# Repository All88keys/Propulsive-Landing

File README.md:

# propulsive-landing
 Arduino Script for HERMES rocket tests

## v0
Test scripts for LEMNOS3 board for Hermes I ("Agon0")

## v1
Test scripts for LEMNOS3 board for Hermes I ("Agon1")

## LEMNOS3
Autodesk EAGLE project for LEMNOS3, logic board design for Hermes I. 
- [Link to EAGLE download](https://www.autodesk.com/products/eagle/overview?plc=F360&term=1-YEAR&support=ADVANCED&quantity=1)
- [Link to MPU 6050](https://www.sparkfun.com/products/11028)

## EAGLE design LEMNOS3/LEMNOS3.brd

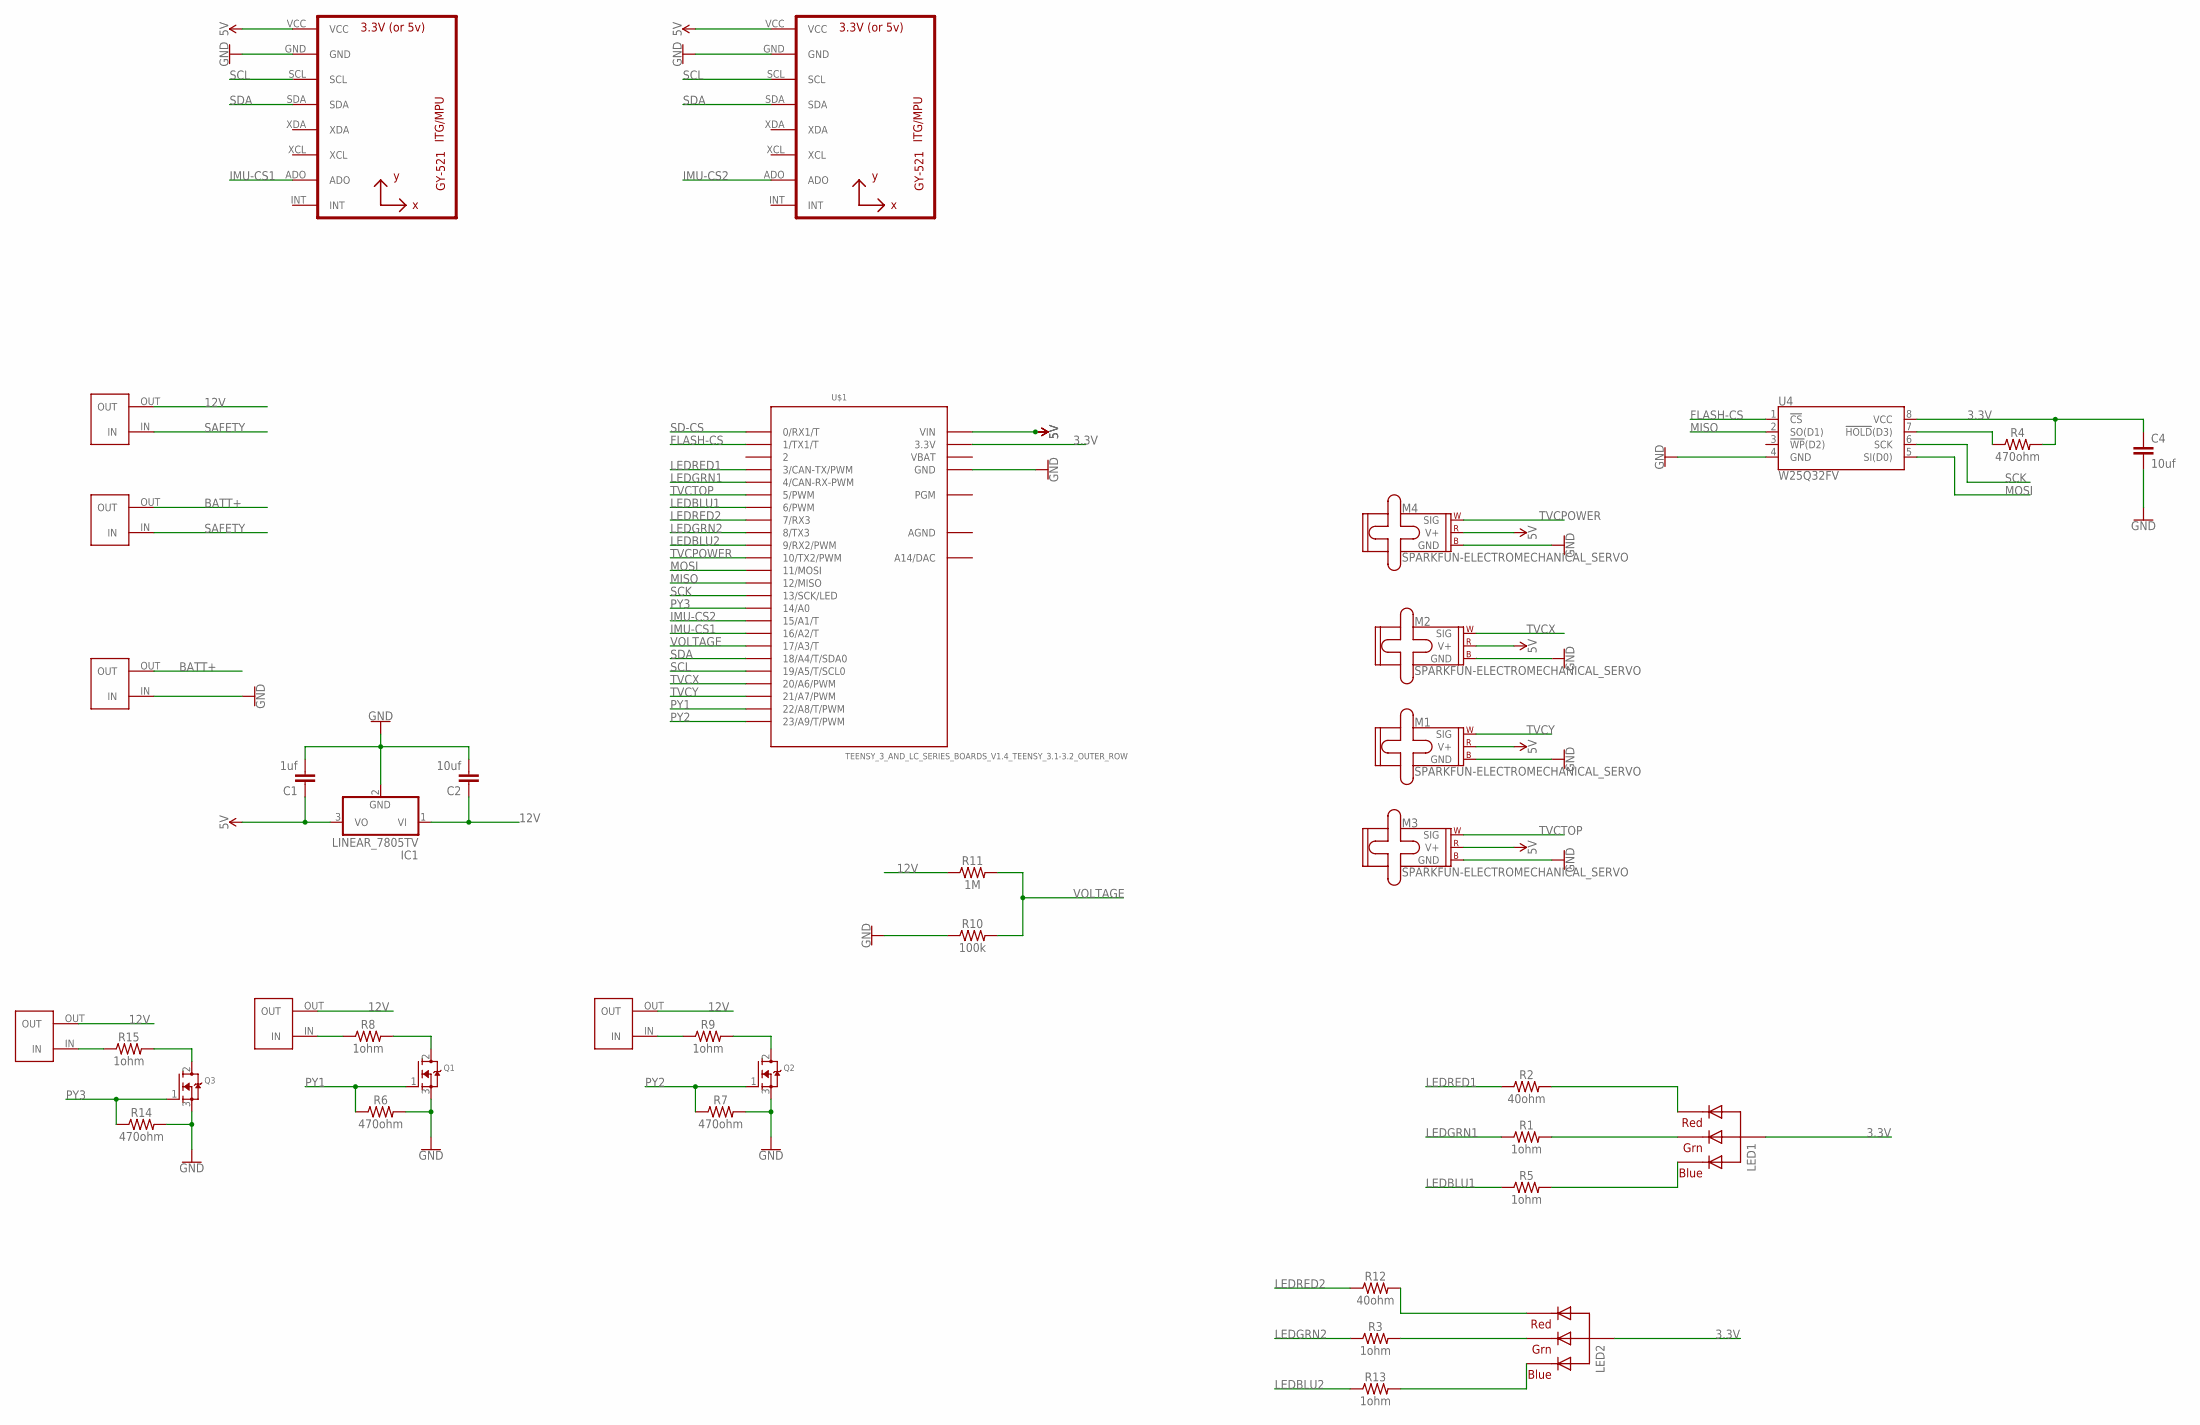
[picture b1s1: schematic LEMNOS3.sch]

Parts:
C1: 1uf; SPARKFUN-CAPACITORS_CAP-PTH-2.54
C2, C4: 10uf; SPARKFUN-CAPACITORS_CAP-PTH-2.54
IC1: LINEAR_7805TV; LINEAR_TO220V
LED1, LED2: RGBLED_CA-5MM; LED5MMRGB
M1, M2, M3, M4: SPARKFUN-ELECTROMECHANICAL_SERVO; SPARKFUN-ELECTROMECHANICAL_1X03
Q1, Q2, Q3: ADAFRUIT_MOSFET-NGDS_TO220V; ADAFRUIT_TO220V
R1, R3, R5, R8, R9, R13, R15: 1ohm; SPARKFUN-RESISTORS_AXIAL-0.3
R2, R12: 40ohm; SPARKFUN-RESISTORS_AXIAL-0.3
R4, R6, R7, R14: 470ohm; SPARKFUN-RESISTORS_AXIAL-0.3
R10: 100k; SPARKFUN-RESISTORS_AXIAL-0.3
R11: 1M; SPARKFUN-RESISTORS_AXIAL-0.3
U1, U2: GY-521_GY-521MPU6050; GY-521_GY-521
U4: W25Q32FV; SPARKFUN-IC-MEMORY_SOIC-8
U$1: TEENSY_3_AND_LC_SERIES_BOARDS_V1.4_TEENSY_3.1-3.2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; TEENSY_3_AND_LC_SERIES_BOARDS_V1.4_TEENSY_3.0-3.2&LC_OUTER_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
U$2, U$3, U$4, U$5, U$6, U$8: BLACKTERMBLOCK_BLACKTERMBLOCK

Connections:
3.3V: C4.1, LED1.2 (VCC), LED2.2 (VCC), R4.P$2 (2), U4.8 (VCC), U$1.3.3V, U$1.3.3V1 (3.3V)
5V: C1.1, IC1.3 (VO), M1.2 (V+), M2.2 (V+), M3.2 (V+), M4.2 (V+), U1.VCC, U2.VCC, U$1.VIN
12V: C2.1, IC1.1 (VI), R11.P$1 (1), U$2.OUT, U$5.OUT, U$6.OUT, U$8.OUT
AGND: U$1.AGND
BATT+: U$3.OUT, U$4.OUT
FLASH-CS: U4.1 (!CS!), U$1.1 (1/TX1/T)
GND: C1.2, C2.2, C4.2, IC1.2 (GND), M1.3 (GND), M2.3 (GND), M3.3 (GND), M4.3 (GND), Q1.3 (S), Q2.3 (S), Q3.3 (S), R6.P$2 (2), R7.P$2 (2), R10.P$1 (1), R14.P$2 (2), U1.GND, U2.GND, U4.4 (GND), U$1.GND, U$1.GND1 (GND), U$3.IN
IMU-CS1: U1.ADO, U$1.16/A2 (16/A2/T)
IMU-CS2: U2.ADO, U$1.15/A1 (15/A1/T)
LEDBLU1: R5.P$1 (1), U$1.6 (6/PWM)
LEDBLU2: R13.P$1 (1), U$1.9 (9/RX2/PWM)
LEDGRN1: R1.P$1 (1), U$1.4 (4/CAN-RX-PWM)
LEDGRN2: R3.P$1 (1), U$1.8 (8/TX3)
LEDRED1: R2.P$1 (1), U$1.3 (3/CAN-TX/PWM)
LEDRED2: R12.P$1 (1), U$1.7 (7/RX3)
MISO: U4.2 (SO(D1)), U$1.12 (12/MISO)
MOSI: U4.5 (SI(D0)), U$1.11 (11/MOSI)
unnamed: R15.P$1 (1), U$2.IN
unnamed: LED1.1 (RED), R2.P$2 (2)
unnamed: R4.P$1 (1), U4.7 (!HOLD!(D3))
unnamed: LED1.3 (GREEN), R1.P$2 (2)
unnamed: LED1.4 (BLUE), R5.P$2 (2)
unnamed: R8.P$1 (1), U$5.IN
unnamed: Q1.2 (D), R8.P$2 (2)
unnamed: LED2.1 (RED), R12.P$2 (2)
unnamed: R9.P$1 (1), U$6.IN
unnamed: Q2.2 (D), R9.P$2 (2)
unnamed: LED2.3 (GREEN), R3.P$2 (2)
unnamed: LED2.4 (BLUE), R13.P$2 (2)
unnamed: Q3.2 (D), R15.P$2 (2)
PY1: Q1.1 (G), R6.P$1 (1), U$1.22/A8 (22/A8/T/PWM)
PY2: Q2.1 (G), R7.P$1 (1), U$1.23/A9 (23/A9/T/PWM)
PY3: Q3.1 (G), R14.P$1 (1), U$1.14/A0
SAFETY: U$4.IN, U$8.IN
SCK: U4.6 (SCK), U$1.13 (13/SCK/LED)
SCL: U1.SCL, U2.SCL, U$1.19/A5 (19/A5/T/SCL0)
SD-CS: U$1.0 (0/RX1/T)
SDA: U1.SDA, U2.SDA, U$1.18/A4 (18/A4/T/SDA0)
TVCPOWER: M4.1 (SIG), U$1.10 (10/TX2/PWM)
TVCTOP: M3.1 (SIG), U$1.5 (5/PWM)
TVCX: M2.1 (SIG), U$1.20/A6 (20/A6/PWM)
TVCY: M1.1 (SIG), U$1.21/A7 (21/A7/PWM)
VBAT: U$1.VBAT
VOLTAGE: R10.P$2 (2), R11.P$2 (2), U$1.17/A3 (17/A3/T)

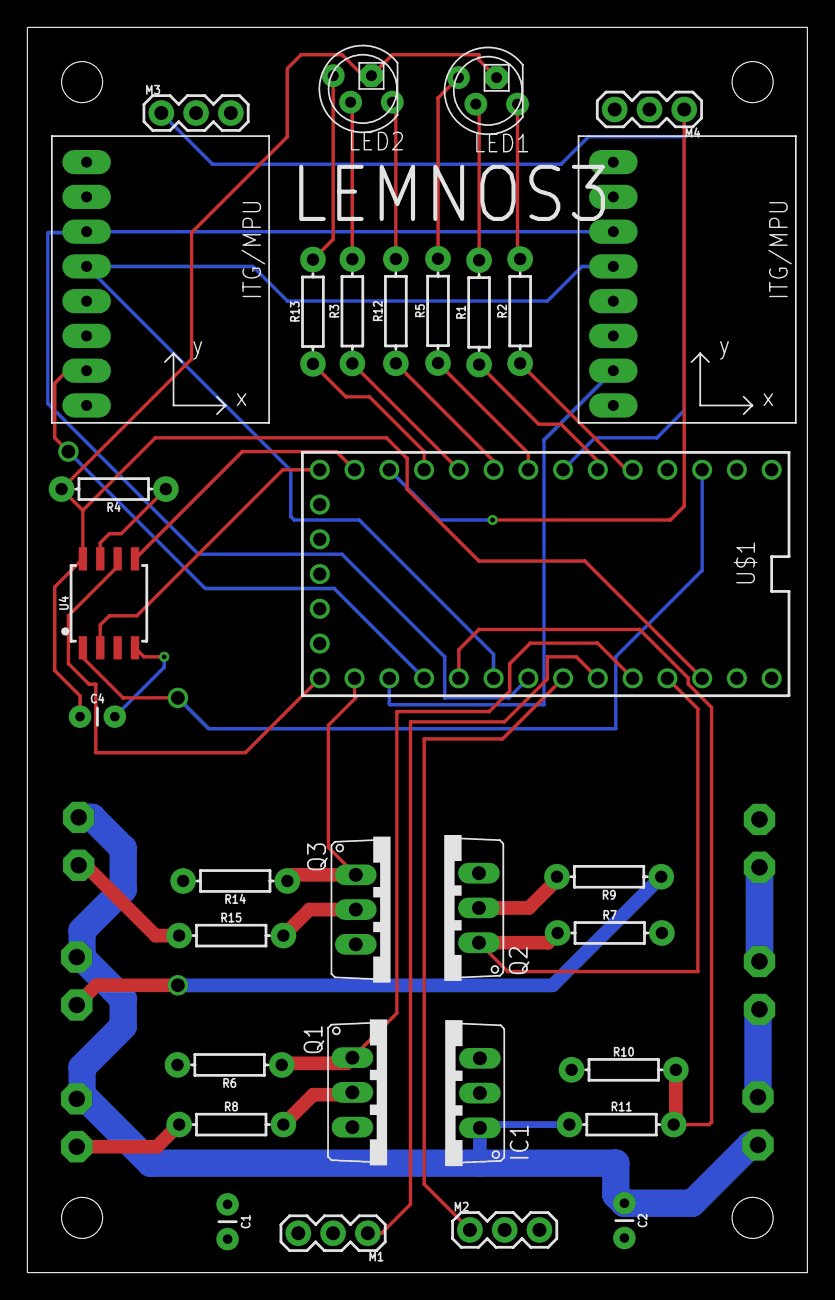
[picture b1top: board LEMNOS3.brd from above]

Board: 2 copper layers, 57.0 x 91.0 mm, 38 parts (0 on the bottom side), 41 nets.

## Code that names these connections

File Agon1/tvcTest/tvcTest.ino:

#include <Servo.h>

//TVC
int TVC_TOP_PIN = 5;
int TVC_X_PIN = 20;
int TVC_Y_PIN = 21;
Servo tvcTop;
Servo tvcX;
Servo tvcY;
int tvcXoffset=85;
int tvcYoffset=83;
//float beta=.9094;
float beta=.6;
int gear=9;
float damper=1.5;
int tvcDelay=10;

long uLast [2]={0, 0};



void setup() {
  // put your setup code here, to run once:
  tvcX.attach(TVC_X_PIN);
  tvcY.attach(TVC_Y_PIN);
  tvcTop.attach(TVC_TOP_PIN);
}

void loop() {
  // put your main code here, to run repeatedly:
    tvc(0, 0, beta, tvcDelay*100);
    /*
    tvc(30, 0, beta, tvcDelay*100);
    tvc(-30, 0, beta, tvcDelay*100);
    tvc(0, 0, beta, tvcDelay*100);
    tvc(0, 30, beta, tvcDelay*100);
    tvc(0, -30, beta, tvcDelay*100);
    tvc(0, 0, beta, tvcDelay*100);
    */
    delay(2000);
}

void tvc(int x, int y, double gamma, int d){
  double u=(x)*cos(gamma)+(y)*sin(gamma);
  double v=(y)*cos(gamma)-(x)*sin(gamma);
  /*
  if (u-uLast[0]>2){
    u=uLast[0]+2;
  }
  else if (u-uLast[0]<-2){
    u=uLast[0]-2;
  }

  if (v-uLast[1]>2){
    v=uLast[1]+2;
  }
  else if (v-uLast[1]<-2){
    v=uLast[1]-2;
  }
  uLast[0]=u; uLast[1]=v;
  */
  tvcY.write(v+tvcYoffset);tvcX.write(u+tvcXoffset); delay(d);
  
}

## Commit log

2020-11-03 Create readme, documentation

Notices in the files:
parts and their libraries:
SparkFun-PowerSymbols: Licensing: Creative Commons ShareAlike 4.0 International - https://creativecommons.org/licenses/by-sa/4.0
